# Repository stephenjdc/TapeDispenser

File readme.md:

# Kilnettle Shrine Souvenir Tape Dispenser

Blog post: https://stephencoyle.net/kilnettle

If you'd like to build your own [tape dispenser](https://stephencoyle.net/kilnettle), which tells you how much you've used, and blesses you afterwards, you have two choices.

1. Leave out a pencil and paper one night before bed, and hope that by the morning God will have written down the instructions.
2. Buy one from me. Maybe? Details coming soon(?)
3. Clone this repo, buy the required parts, a 3D printer, and get to work. [Here's an assembly tutorial](https://youtu.be/CnwMDydeqiA).

Please note that, while the dispenser does aim to fairly accurate, it's not perfectly accurate as it doesn't adjust for the amount of tape used. In the code I've just split the error, so it will tend to overshoot the measurement when a roll is full, and undershoot a bit when it's empty. Given we're only dealing with one-inch resolution, I feel like it's probably fine. You can tweak the code if you want to try and improve on this. There's also is a no-code way to tweak it, detailed below.

## License 
Feel free to make/reuse/modify this project for personal use. In the unlikely event that you're planning to spin up a large-scale production line to make thousands of these, I'd really recommend doing a few more revisions on the code and the models. In which case, I'm available at a very reasonable rate.

## Parts list

### Electronics
- 1× ESP8266 or similar (e.g. I used an ESP-12E)
- 1× IR photodiode (3mm)
- 1× IR LED (3mm)
- 2× 1k resistors
- 2× 10k resistors
- 1× 220Ω resistor
- 1× 2N3904 transistor (or similar)
- 1× LED (colour of your choice, I recommend red)
- 1× 20mm diameter speaker
- 1× 18mm × 12mm slide switch (or any that fits the space on the model)
- Battery clips for 2x AAA batteries

There are included KiCAD files which you can use to create a PCB for this, but point-to-point soldering can also work if you don't want to do that.

#### PCB Legend
| PCB Label | Component | Description |
|---|---|---|
| `R1` | `1K resistor` | |
| `R2` | `220R resistor` | |
| `R3` | `1K resistor` | |
| `R4` | `10K resistor` | |
| `R5` | `10K resistor` | |
| `D1` | `Photodiode` | Small black LED |
| `D2` | `IR LED` |  Small clear LED |
| `D3` | `Indicator LED` | Red LED |
| `LS1` | `Speaker` |  |
| `Q1` | `2N3904 Transistor` |  |
| `U1` | `ESP8266` |  |
| `J1` | `GND` |  |
| `J2` | `+3V` | |

### Dispenser body
#### These parts are 3D-printable (in the models folder)
- 1× tape dispenser body
- 1× tape dispenser lid (which holds the spool)
- 1× battery compartment cover
- 1× tape spool
- 1× "Greetings from Kilnettle" text

#### These parts are not 3D printable
- 1× 33mm × 5mm hacksaw blade (for tape cutter)
- 1x 25mm × 1mm steel rod (for example, cut from a large paperclip)
- 2× AAA batteries
- 1x roll of sticky tape with ~27mm inner diameter and ~56mm outer diameter. I used [this one](https://firstclassofficesupplies.com/product/stik-ie-clear-tape-refills/).

## Instructions
I'm gonna keep these fairly sparse, and following what I did. But there's no right way to do it. In the very unlikely event that you actually want to make one yourself, and run into trouble, feel free to message me with any questions. The [video version](https://youtu.be/CnwMDydeqiA) may also be more useful!

1. Flash the ESP-12E with the included sketch, _and data folder_. I used PlatformIO and would suggest you do too.
2. 3D print the included files.
3. Insert the battery clips into the slots in the battery container. Note which side has holes for the positive and negative tabs to slot into.
4. Fit the slider switch into the hole above the battery compartment. Either glue into place, or like I did, use a soldering iron to melt and smush the little nubs to fix it in place.
5. Fit the IR photodiode and LED into the holes on the sides of the lid. They should be a fairly tight fit; push them all the way in. I added a little drop of superglue to keep them fixed in place.
6. Add the speaker. It should click into place at the front of the body, though I added a little hot glue just to be sure. If you aren't using the PCB, it might be easier to add the transistor and resistor on or near the speaker itself, then tuck all that in with the speaker.
7. Solder some wires to the battery tabs and switch.
8. Follow the rest of the schematic to attach all the parts. If you aren't using the PCB, use the thinnest wire you feasibly can, and route the wires as best you can to allow the case to close. I'd recommend leaving a decent bit of slack, and regularly trying to fit the lid on to make sure all is fitting well.
9. Once that's done, I'd recommend testing it out[^1], so you can check the software is flashed properly before you finish fitting things into place.
10. Pop on the lid, if you're happy everything is working. The tabs at the back should clip into place in the case.
11. Superglue the section of hacksaw blade in place on the front of dispenser. Make sure to put the sharper side facing up, if there is one, so it cuts the tape nicely.
12. Attach the "Greetings from Kilnettle" text to the left side of the dispenser body (left when looking at the bladed end).
13. For the spool, thread the steel rod through the hole in its centre. Add a drop of glue and line it up so that it protrudes an equal amount on either side. It should then press fit into the tape, and you can set it into the dispenser.
14. Insert batteries (be careful to put them in the right way round), pop on the battery cover, and all being well, you should now be able to switch it on and enjoy your dispenser!

[^1]: You can easily test it without a spool, by waving your finger around in the spool cavity, making sure you block the IR beam a few times.

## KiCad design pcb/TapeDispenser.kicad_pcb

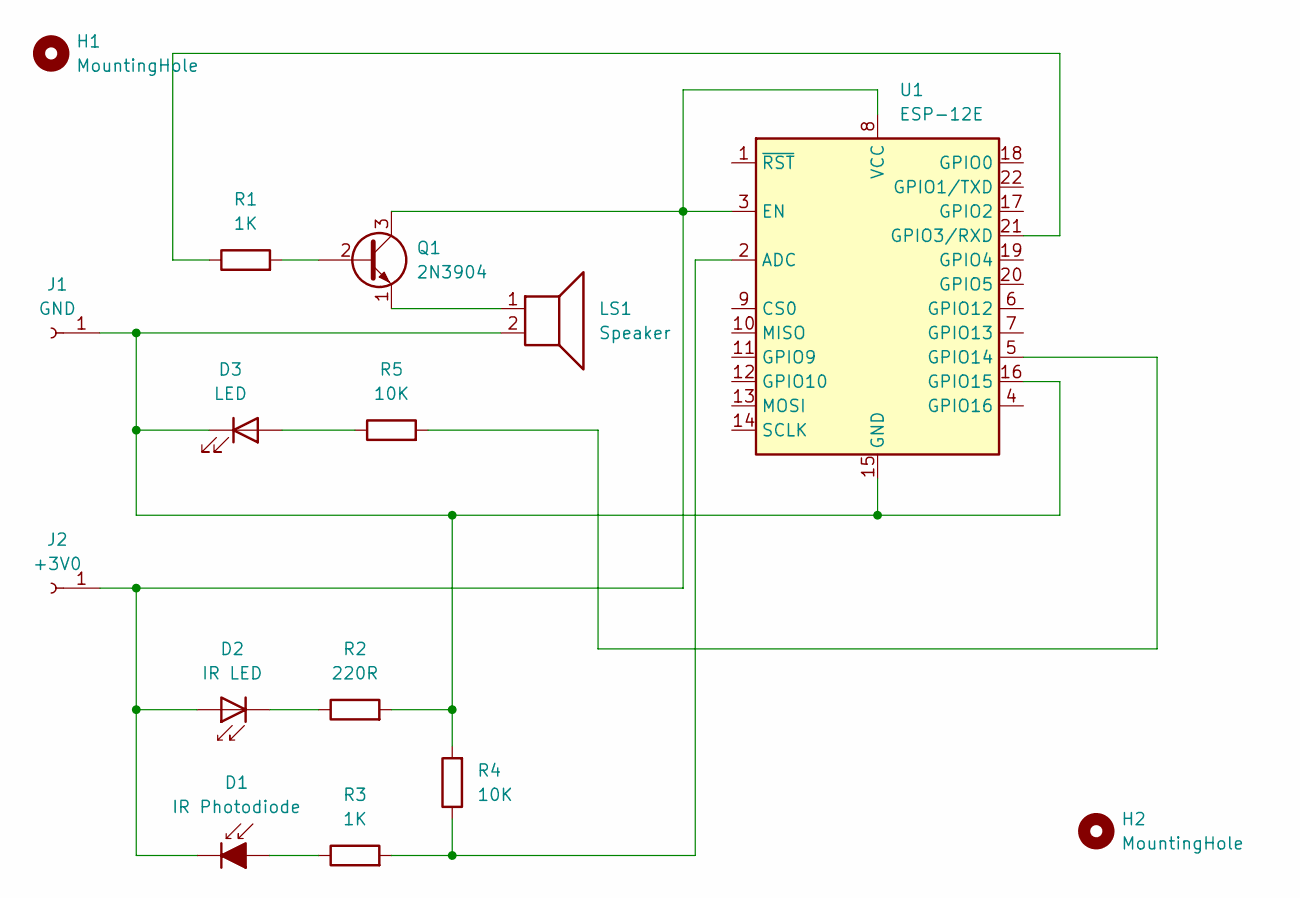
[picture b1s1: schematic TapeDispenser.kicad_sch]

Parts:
D1: IR Photodiode; SolderWire-0.5sqmm_1x02_P4.6mm_D0.9mm_OD2.1mm
D2: IR LED; SolderWire-0.5sqmm_1x02_P4.6mm_D0.9mm_OD2.1mm
D3: LED; SolderWire-0.5sqmm_1x02_P4.6mm_D0.9mm_OD2.1mm
H1, H2: MountingHole; MountingHole_2.2mm_M2
J1: GND; SolderWire-0.5sqmm_1x01_D0.9mm_OD2.1mm
J2: +3V0; SolderWire-0.5sqmm_1x01_D0.9mm_OD2.1mm
LS1: Speaker; SolderWire-0.5sqmm_1x02_P4.6mm_D0.9mm_OD2.1mm
Q1: 2N3904; TO-92_Inline
R1, R3: 1K; R_Axial_DIN0207_L6.3mm_D2.5mm_P10.16mm_Horizontal
R2: 220R; R_Axial_DIN0207_L6.3mm_D2.5mm_P10.16mm_Horizontal
R4, R5: 10K; R_Axial_DIN0207_L6.3mm_D2.5mm_P10.16mm_Horizontal
U1: ESP-12E

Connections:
unnamed: D1.2 (A), R3.1
unnamed: D1.1 (K), D2.2 (A), J2.1, Q1.3 (C), U1.3 (EN), U1.8 (VCC)
unnamed: D2.1 (K), R2.1
unnamed: D3.2 (A), R5.1
unnamed: D3.1 (K), J1.1, LS1.2, R2.2, R4.2, U1.15 (GND), U1.16 (GPIO15)
unnamed: Q1.2 (B), R1.2
unnamed: LS1.1, Q1.1 (E)
unnamed: R3.2, R4.1, U1.2 (ADC)
unnamed: R1.1, U1.21 (GPIO3/RXD)
unnamed: R5.2, U1.5 (GPIO14)

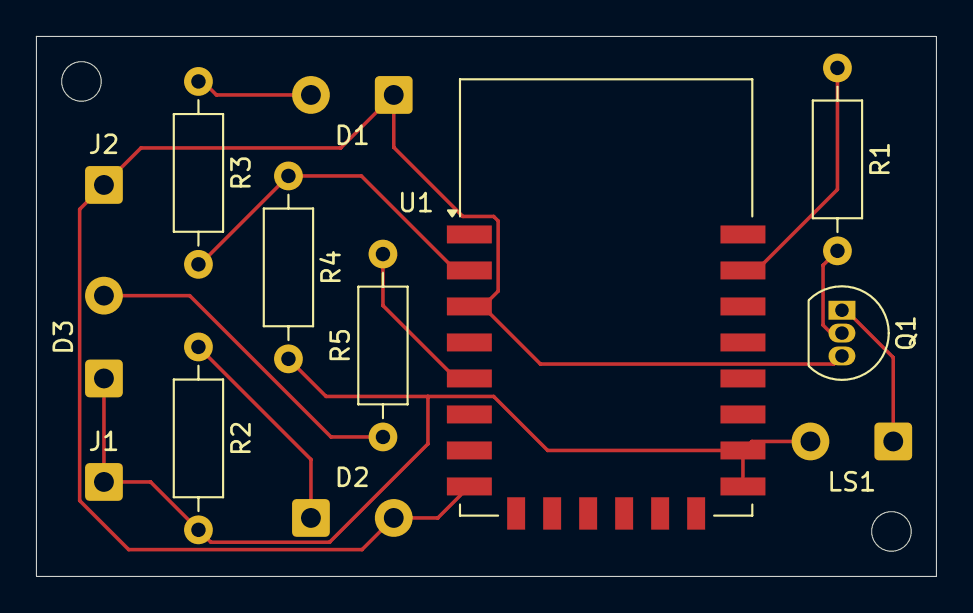
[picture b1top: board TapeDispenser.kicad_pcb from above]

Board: 2 copper layers, 50.0 x 30.0 mm, 15 parts (0 on the bottom side), 10 nets.

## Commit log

2024-03-02 debug mode
2024-03-08 added debug stuff
2024-03-08 Changed from interrupt to polling analog value
2024-03-09 added test audio playback
2024-03-09 Audio file queueing
2024-04-22 Calibration, disabled debug code, other tweaks
2024-04-22 New audio files, better sensor algorithm
    + other improvements to code
2024-04-22 Added 3D models and readme, cleanup
2024-06-07 Updated battery door, new spool design
2024-07-05 Added schematic, instructions and updated battery model.
2025-02-14 Package update and baud rate change
2025-06-01 updated models and instructions
2025-06-01 instruction updates
2025-06-01 Updated gitignore
2025-07-09 More reliable spool design
